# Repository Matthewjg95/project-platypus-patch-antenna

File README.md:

# Project Platypus — 2.4 GHz Microstrip Patch Antenna

A directional 2.4 GHz patch antenna on 2-layer FR4, designed from first principles —
no antenna generator, no reference design, no copied footprint. Every dimension is
derived from the cavity model and Hammerstad–Jensen microstrip synthesis, then
validated on manufactured hardware over a real RF link.

**Status: manufactured and functional. Gain vs the host's internal antenna is not
yet characterised.**

An early measurement produced an anomalously high delta and was excluded from
conclusions pending repeatability. Characterisation is in progress under a
controlled procedure — see [`TEST_PROCEDURE.md`](TEST_PROCEDURE.md) and
[`VNA_TEST_PLAN.md`](VNA_TEST_PLAN.md).

**Commercialization milestone:** On September 4, 2026, the Rev 2 development
project was **approved** for the Tindie × NextPCB Hardware Creator R&D Support
Program after applying on August 30. The award provides three monthly rounds of
standalone PCB-prototyping and international-shipping support. Rev 2 remains an
engineering-validation build: a sales listing is still gated on design review,
DFM, repeatable RF testing, and pilot-readiness evidence. Later support rounds
may be redirected to Platypus One carrier-board fabrication if the antenna
converges without another justified spin. See [`MILESTONES.md`](MILESTONES.md).

> Board photos: the panel is purple ENIG and photographs beautifully — see the Hackster
> project this repo accompanies.

---

## The board

One 58 × 210 mm V-scored panel, three antennas. Each board is 58 × 70 mm with an
M3 mounting pattern (44 mm square, matching the M5Tab5), a 50 Ω microstrip feed, and an
edge-launch MMCX jack (Cinch/Johnson 135-3711-801) seated in a routed notch.

### Why three designs on one panel

Impedance matching a patch has two textbook solutions. Rather than pick one on faith,
the panel carries **all three variants side by side** — same substrate, same fab run,
directly comparable:

| Design | Matching method | Geometry | Predicted Rin |
|---|---|---|---|
| **A** | Inset feed, calculated match | y₀ = 9.81 mm, slot 6.3 mm | 50 Ω (matched) |
| **B** | Inset feed, deliberate mismatch | y₀ = 7.50 mm, slot 6.3 mm | 97 Ω (control) |
| **C** | Quarter-wave transformer | Z_t = 100 Ω, w = 0.709 mm, ℓ = 17.98 mm | 50 Ω via λ/4 |

Design B is intentionally mismatched — the control that tests whether the matching
model is doing what the math claims.

---

## Design math (all first-principles)

Substrate: FR4, h = 1.6 mm, εr = 4.4, tan δ ≈ 0.02, 2 layers, ENIG.

```
Patch width      W = c/(2f₀)·√(2/(εr+1))                    = 38.04 mm
Effective εr     εr_eff = (εr+1)/2 + (εr−1)/2·(1+12h/W)^−½   = 4.086
Fringing ext.    ΔL = 0.412h·((εr_eff+0.3)(W/h+0.264)) /
                          ((εr_eff−0.258)(W/h+0.8))         = 0.742 mm
Patch length     L = c/(2f₀√εr_eff) − 2ΔL                    = 29.44 mm
50 Ω feed width  (Hammerstad–Jensen, FR4 1.6 mm)             = 3.1 mm
Inset depth      Rin(y₀) = Rin_edge·cos²(πy₀/L) → 50 Ω       = 9.81 mm
λ/4 transformer  Z_t = √(50·200) = 100 Ω, w = 0.709 mm, ℓ    = 17.98 mm
```

Resonance check: L_eff = 29.44 + 2(0.742) = 30.924 mm, √εr_eff = 2.021
→ **f₀ = 2.3996 GHz**.

**Inset slot width follows the Salmony method:** clearance each side of the feed must be
≥ the substrate height h, giving a 6.3 mm total slot (3.1 + 2×1.6). A slot barely wider
than the feed is a common mistake that creates spurious resonances and spoils the match.

### Honest analysis notes

- **Return loss is not signal loss.** A mismatch costs only 10·log₁₀(1−|Γ|²): even
  Design B's deliberate 97 Ω feed point loses well under 2 dB of delivered power. The
  A/B/C comparison therefore needs an S11 sweep (VNA), not RSSI — whatever advantage a
  patch shows over a chip antenna comes from directivity and escaping the host
  enclosure, not from matching finesse.
- **Front-to-back is modest by design.** The ground plane extends only 10–12 mm
  (≈0.1 λ) past the patch, so realistic F/B is ~6–10 dB. Fine for "point the gain at
  the far node"; don't expect a deep rear null indoors.

---

## Manufacturing notes (learned on real hardware)

- **ENIG is required** — HASL's uneven surface degrades RF pads.
- JLCPCB parses V-score geometry from **Edge.Cuts/GM1 only** — order notes and
  Dwgs.User lines are ignored. Their V-cut minimum panel size is 70 × 70 mm.
- The Edge.Cuts outline must be closed loops with exactly two segments per vertex; the
  MMCX notches are separate internal rectangles sharing no vertices with the perimeter.
- The MMCX signal pad sits inside the routed notch — contact is made by the connector's
  spring pin, and the corresponding DRC "unconnected" items are by design (waived in
  `patch_antenna_smp.kicad_dru` / DRC exclusions).
- Solder mask over the radiator shifts resonance down slightly (~10–30 MHz) but does
  not prevent operation.

## Repository layout

This repo now carries the **full project**, not just the manufactured revision — see
[`PROJECT_STATUS.md`](PROJECT_STATUS.md) for the live status, revision map, and
open decisions.

```
patch_antenna_smp.kicad_pcb      Rev 7.13.1 — the MANUFACTURED revision (do not edit)
gerbers/  +  gerbers.zip         Rev 7.13.1 fab package as manufactured (JLCPCB)
DRC7.13.1.rpt                    DRC report of the manufactured revision
patch_antenna_smp_rev8.*         Rev 8 — 3×3 panel respin (lessons-learned; superseded)
patch_antenna_smp_rev9.*         Rev 9 — dual SMT connector lands (u.FL + MMCX); current
rev9_fab/ + rev9_gerbers_jlcpcb.zip   Rev 9 JLCPCB fab+assembly package (BOM/CPL included)
rev8_backups/, rev9_backups/     Staged design snapshots (rollback points)
REV8_PLAN.md, REV9_CONNECTORS.md Revision change logs & design decisions
DESIGN_915_MESHTASTIC.md         915 MHz Meshtastic/LoRa patch — design study
DESIGN_NOTES_v72.md              Full first-principles derivation, BOM, fab notes
TEST_PROCEDURE.md                Over-the-air RF test protocol
VNA_TEST_PLAN.md                 Bench characterisation milestones (S11, gain, pattern)
PROJECT_STATUS.md                Current state, toolchain notes, transfer guide
BOM/Links.txt                    Component sourcing
```

## Bill of materials (per board)

| Ref | Part | Notes |
|---|---|---|
| J1 | MMCX 135-3711-801 (Cinch/Johnson) | Edge-launch jack, board notch |
| H1–H4 | M3 × 6 mm screw + 5 mm nylon standoff | Nylon preferred for RF isolation |
| — | Pigtail: SMP-male → MMCX-male, RG178, ~100 mm | Host-device dependent |

**Fab settings:** 2-layer FR4 1.6 mm, ENIG, purple mask, white silk,
V-score at 70 mm and 140 mm from panel top.

## License

Hardware and documentation are released under the
**[CERN Open Hardware Licence v2 — Strongly Reciprocal](LICENSE)** (CERN-OHL-S v2).
You may use, study, modify, manufacture and sell this design, provided derivative
hardware designs are shared under the same terms.

---

*Project Platypus — Open Source RF*

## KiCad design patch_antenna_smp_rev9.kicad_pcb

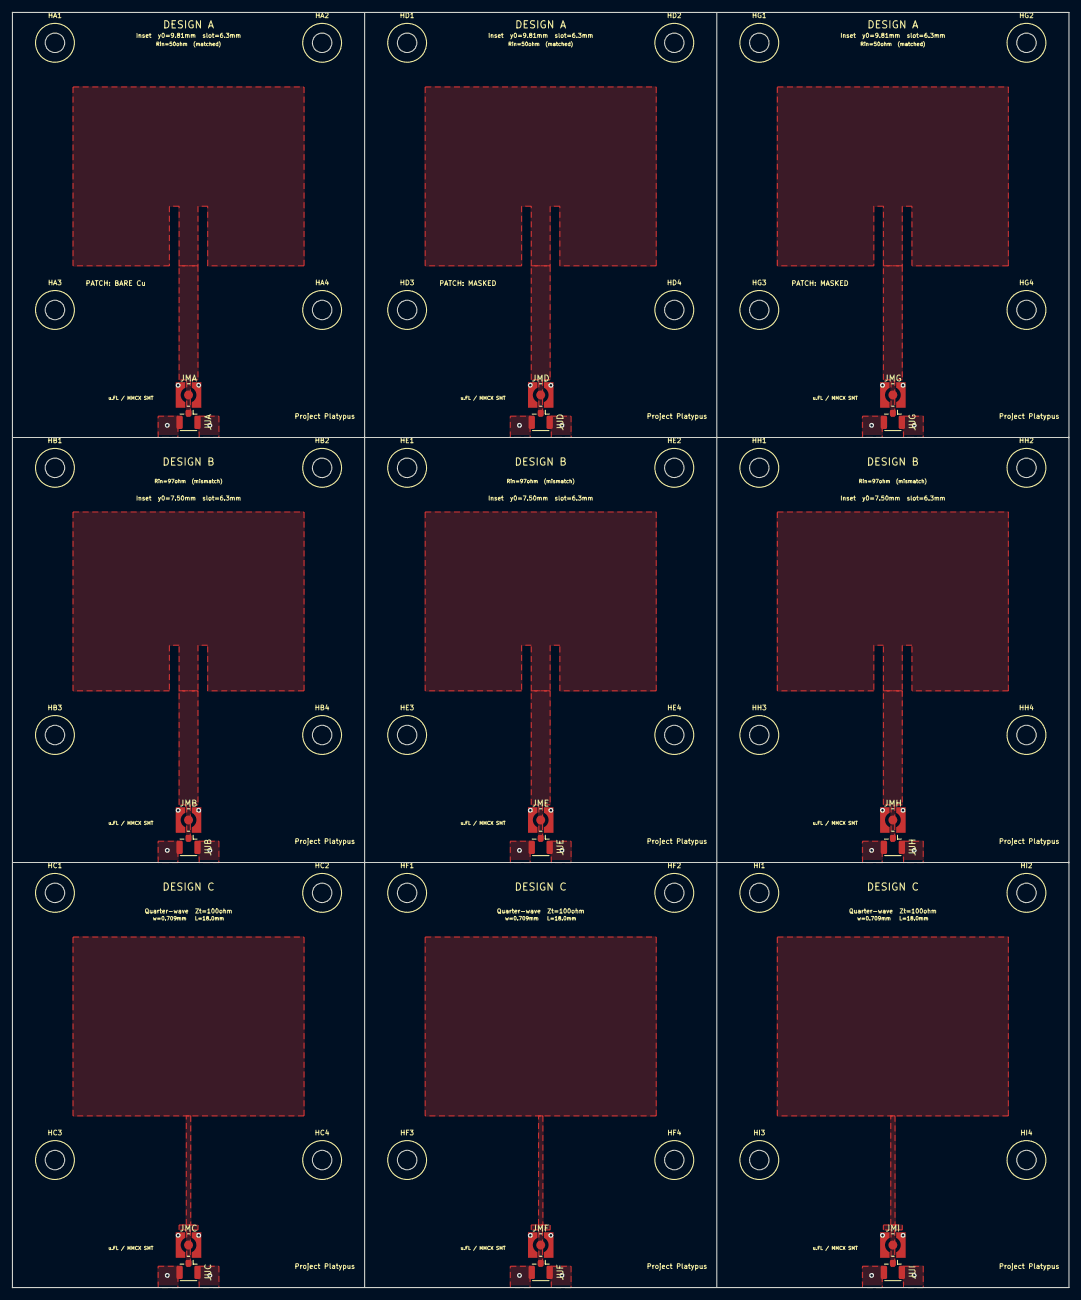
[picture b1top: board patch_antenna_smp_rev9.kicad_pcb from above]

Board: 2 copper layers, 174.0 x 210.0 mm, 54 parts (0 on the bottom side), 2 nets, no tracks yet.

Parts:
HA1, HA2, HA3, HA4: M3; M3_NPTPH
HB1, HB2, HB3, HB4: M3; M3_NPTPH
HC1, HC2, HC3, HC4: M3; M3_NPTPH
HD1, HD2, HD3, HD4: M3; M3_NPTPH
HE1, HE2, HE3, HE4: M3; M3_NPTPH
HF1, HF2, HF3, HF4: M3; M3_NPTPH
HG1, HG2, HG3, HG4: M3; M3_NPTPH
HH1, HH2, HH3, HH4: M3; M3_NPTPH
HI1, HI2, HI3, HI4: M3; M3_NPTPH
JMA: WR-MMCX 66012102111404; WR-MMCX_Wuerth_66012102111404_Vertical
JMB: WR-MMCX 66012102111404; WR-MMCX_Wuerth_66012102111404_Vertical
JMC: WR-MMCX 66012102111404; WR-MMCX_Wuerth_66012102111404_Vertical
JMD: WR-MMCX 66012102111404; WR-MMCX_Wuerth_66012102111404_Vertical
JME: WR-MMCX 66012102111404; WR-MMCX_Wuerth_66012102111404_Vertical
JMF: WR-MMCX 66012102111404; WR-MMCX_Wuerth_66012102111404_Vertical
JMG: WR-MMCX 66012102111404; WR-MMCX_Wuerth_66012102111404_Vertical
JMH: WR-MMCX 66012102111404; WR-MMCX_Wuerth_66012102111404_Vertical
JMI: WR-MMCX 66012102111404; WR-MMCX_Wuerth_66012102111404_Vertical
JUA: U.FL-R-SMT-1; U.FL_Hirose_U.FL-R-SMT-1_Vertical
JUB: U.FL-R-SMT-1; U.FL_Hirose_U.FL-R-SMT-1_Vertical
JUC: U.FL-R-SMT-1; U.FL_Hirose_U.FL-R-SMT-1_Vertical
JUD: U.FL-R-SMT-1; U.FL_Hirose_U.FL-R-SMT-1_Vertical
JUE: U.FL-R-SMT-1; U.FL_Hirose_U.FL-R-SMT-1_Vertical
JUF: U.FL-R-SMT-1; U.FL_Hirose_U.FL-R-SMT-1_Vertical
JUG: U.FL-R-SMT-1; U.FL_Hirose_U.FL-R-SMT-1_Vertical
JUH: U.FL-R-SMT-1; U.FL_Hirose_U.FL-R-SMT-1_Vertical
JUI: U.FL-R-SMT-1; U.FL_Hirose_U.FL-R-SMT-1_Vertical

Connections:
GND: JMA.2, JMB.2, JMC.2, JMD.2, JME.2, JMF.2, JMG.2, JMH.2, JMI.2, JUA.2, JUB.2, JUC.2, JUD.2, JUE.2, JUF.2, JUG.2, JUH.2, JUI.2
RF_IN: JMA.1, JMB.1, JMC.1, JMD.1, JME.1, JMF.1, JMG.1, JMH.1, JMI.1, JUA.1, JUB.1, JUC.1, JUD.1, JUE.1, JUF.1, JUG.1, JUH.1, JUI.1

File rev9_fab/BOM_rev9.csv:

Comment,Designator,Footprint,LCSC Part #
U.FL-R-SMT-1(10),"JUD,JUE,JUF",U.FL_Hirose_U.FL-R-SMT-1_Vertical,C88373
WR-MMCX 66012102111404,"JMA,JMB,JMC,JMG,JMH,JMI",WR-MMCX_Wuerth_66012102111404_Vertical,GLOBAL-SOURCING (Wurth 66012102111404)

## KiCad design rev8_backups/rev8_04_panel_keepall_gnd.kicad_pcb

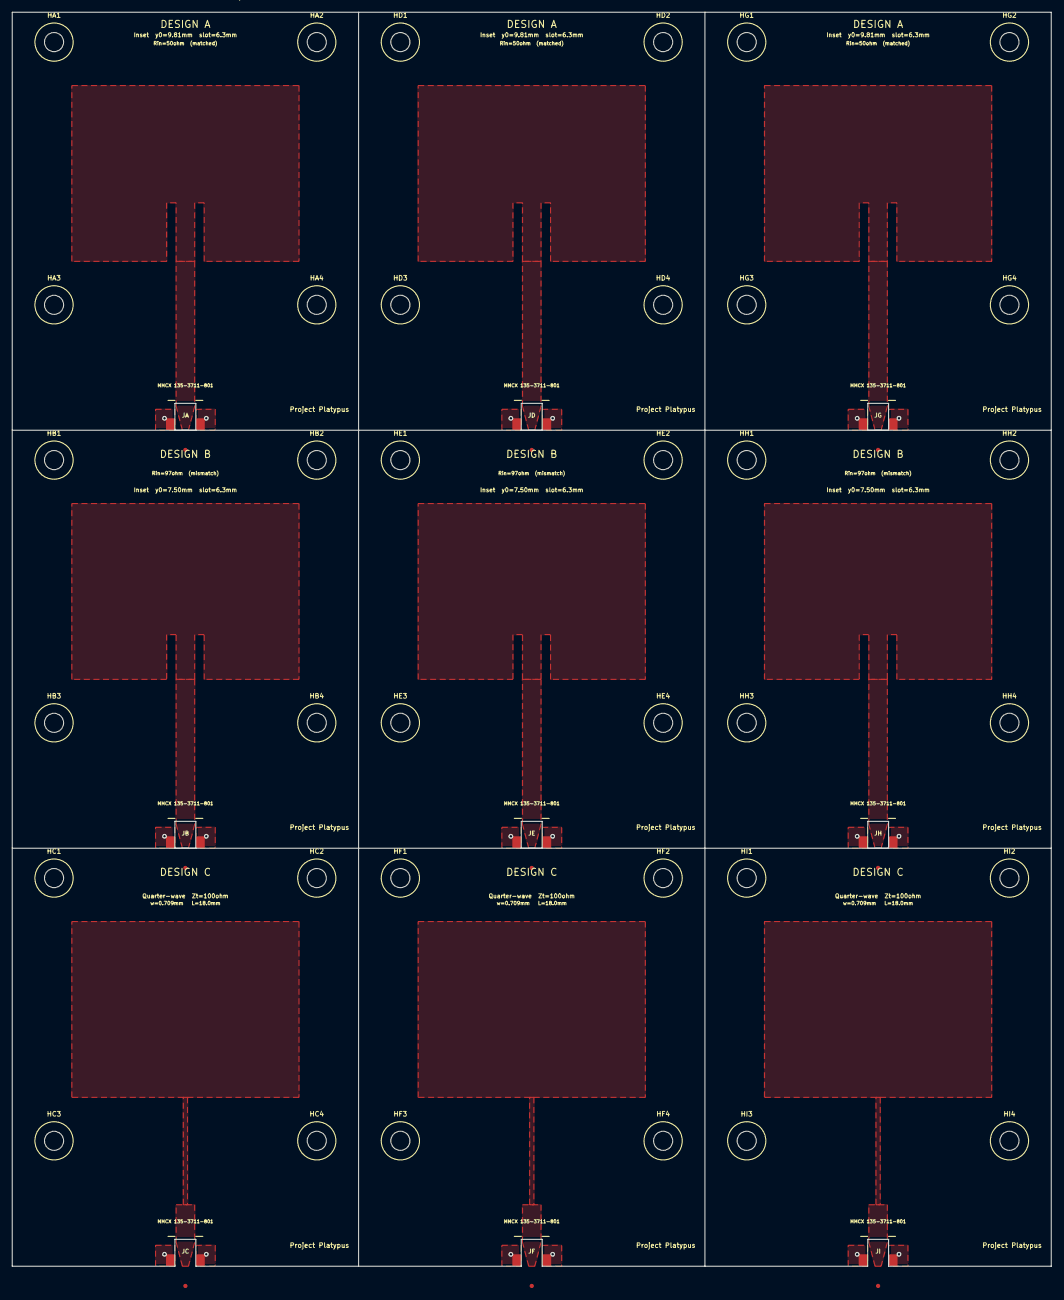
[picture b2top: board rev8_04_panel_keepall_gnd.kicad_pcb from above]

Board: 2 copper layers, 174.0 x 210.0 mm, 45 parts (0 on the bottom side), 2 nets, no tracks yet.

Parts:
HA1, HA2, HA3, HA4: M3; M3_NPTPH
HB1, HB2, HB3, HB4: M3; M3_NPTPH
HC1, HC2, HC3, HC4: M3; M3_NPTPH
HD1, HD2, HD3, HD4: M3; M3_NPTPH
HE1, HE2, HE3, HE4: M3; M3_NPTPH
HF1, HF2, HF3, HF4: M3; M3_NPTPH
HG1, HG2, HG3, HG4: M3; M3_NPTPH
HH1, HH2, HH3, HH4: M3; M3_NPTPH
HI1, HI2, HI3, HI4: M3; M3_NPTPH
JA: MMCX-135-3711-801; MMCX_135-3711-801
JB: MMCX-135-3711-801; MMCX_135-3711-801
JC: MMCX-135-3711-801; MMCX_135-3711-801
JD: MMCX-135-3711-801; MMCX_135-3711-801
JE: MMCX-135-3711-801; MMCX_135-3711-801
JF: MMCX-135-3711-801; MMCX_135-3711-801
JG: MMCX-135-3711-801; MMCX_135-3711-801
JH: MMCX-135-3711-801; MMCX_135-3711-801
JI: MMCX-135-3711-801; MMCX_135-3711-801

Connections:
GND: JA.2, JA.3, JB.2, JB.3, JC.2, JC.3, JD.2, JD.3, JE.2, JE.3, JF.2, JF.3, JG.2, JG.3, JH.2, JH.3, JI.2, JI.3
RF_IN: JA.1, JB.1, JC.1, JD.1, JE.1, JF.1, JG.1, JH.1, JI.1

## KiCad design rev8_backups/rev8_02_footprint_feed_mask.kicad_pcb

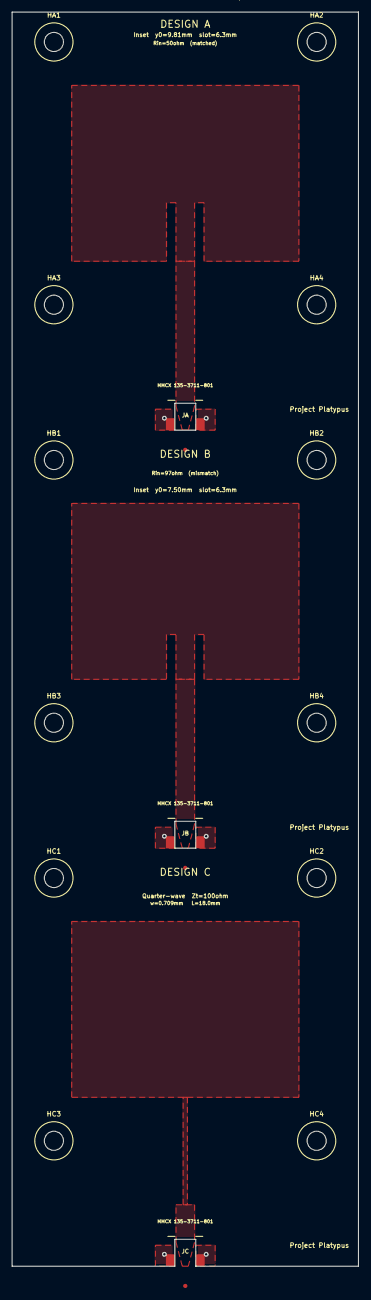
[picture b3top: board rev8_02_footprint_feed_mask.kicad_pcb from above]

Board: 2 copper layers, 58.0 x 210.0 mm, 15 parts (0 on the bottom side), 2 nets, no tracks yet.

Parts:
HA1, HA2, HA3, HA4: M3; M3_NPTPH
HB1, HB2, HB3, HB4: M3; M3_NPTPH
HC1, HC2, HC3, HC4: M3; M3_NPTPH
JA: MMCX-135-3711-801; MMCX_135-3711-801
JB: MMCX-135-3711-801; MMCX_135-3711-801
JC: MMCX-135-3711-801; MMCX_135-3711-801

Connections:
GND: JA.2, JA.3, JB.2, JB.3, JC.2, JC.3
RF_IN: JA.1, JB.1, JC.1
